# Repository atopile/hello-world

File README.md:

# hello-world

Wooohooo a new package!

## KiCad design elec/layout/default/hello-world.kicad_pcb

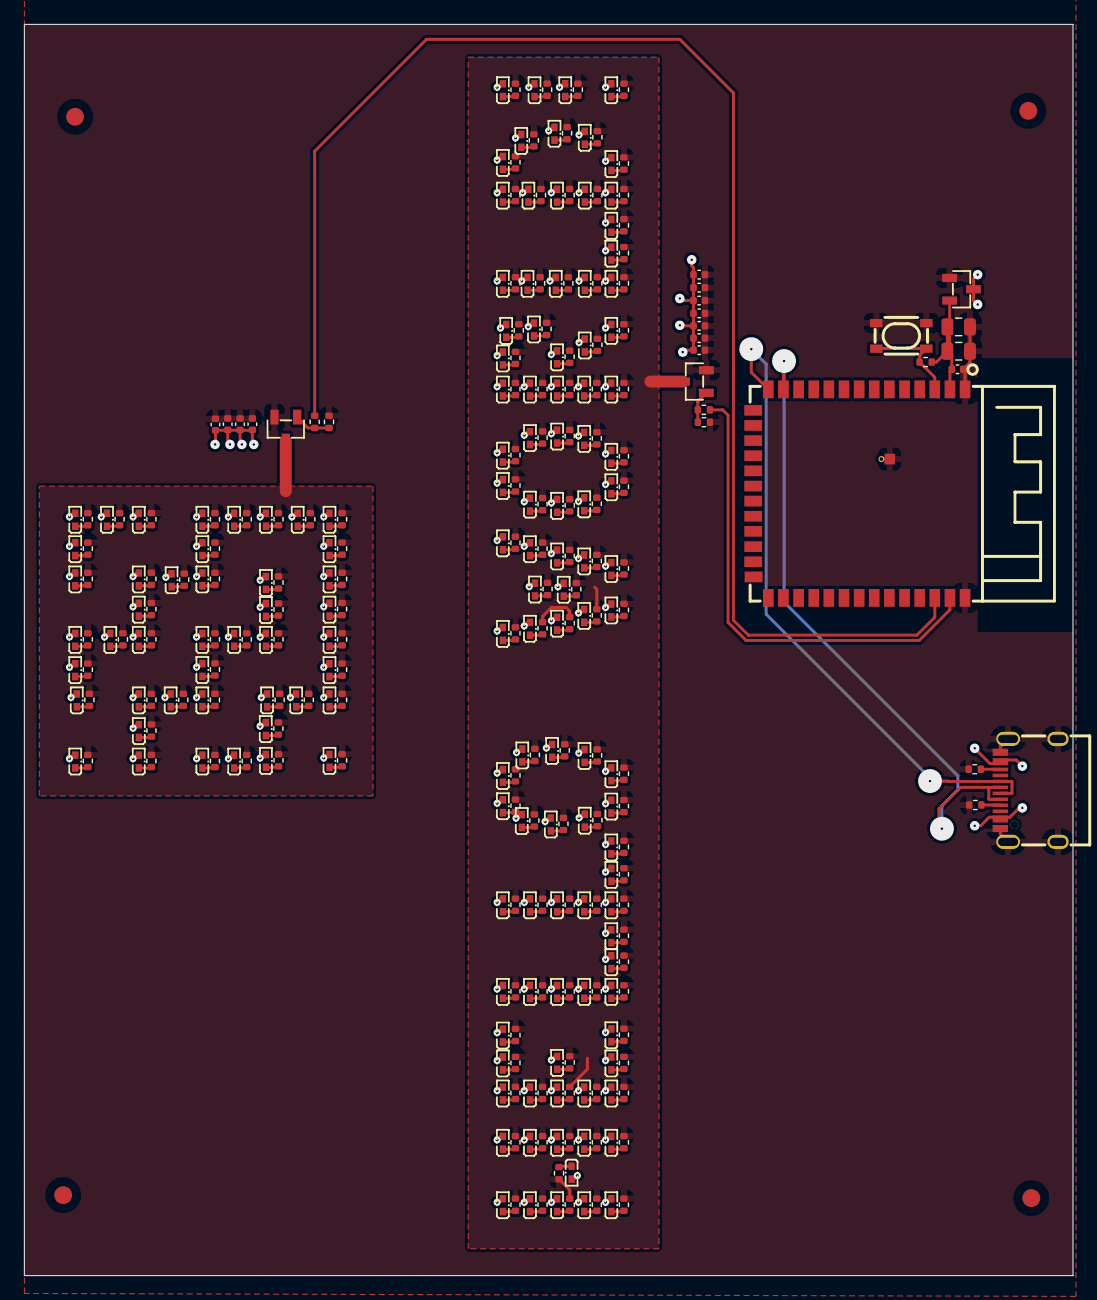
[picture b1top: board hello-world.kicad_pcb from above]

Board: 2 copper layers, 88.0 x 105.0 mm, 319 parts (0 on the bottom side), 158 nets.

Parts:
C1, C5, C6, C7, C8, C9, C10, C11, C12, C13, C14: 25V 1uF X5R ±10% 0402 Multilayer Ceramic Capacito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; C0402
C2: 16V 100nF X7R ±10% 0402 Multilayer Ceramic Capaci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; C0402
C3, C4: 25V 10uF X5R ±10% 0805 Multilayer Ceramic Capacit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; C0805
FID1, FID2, FID3, FID4: Fiducial_1.5mm_Mask3mm
LED1, LED2, LED3, LED4, LED5, LED6, LED7, LED8, LED9, LED10, LED11, LED12, LED13, LED14, LED15, LED16, LED17, LED18, LED19, LED20, LED21, LED22, LED23, LED24, LED25, LED26, LED27, LED28, LED29, LED30, LED31, LED32, LED33, LED34, LED35, LED36, LED37, LED38, LED39, LED40, LED41, LED42, LED43, LED44, LED45, LED46, LED47, LED48, LED49, LED50, LED51, LED52, LED53, LED54, LED55, LED56, LED57, LED58, LED59, LED60, LED61, LED62, LED63, LED64, LED65, LED66, LED67, LED68, LED69, LED70, LED71, LED72, LED73, LED74, LED75, LED76, LED77, LED78, LED79, LED80, LED81, LED82, LED83, LED84, LED85, LED86, LED87, LED88, LED89, LED90, LED91, LED92, LED93, LED94, LED95, LED96, LED97, LED98, LED99, LED100, LED101, LED102, LED103, LED104, LED105, LED106, LED107, LED108, LED109, LED110, LED111, LED112, LED113, LED114, LED115, LED116, LED117, LED118, LED119, LED120, LED121, LED122, LED123, LED124, LED125, LED126, LED127, LED128, LED129, LED130, LED131, LED132, LED133, LED134, LED135, LED136, LED137, LED138, LED139, LED140, LED141, LED142, LED143, LED144: ?; LED0402-RD_ORANGE
Q1, Q2: ?; SOT-23-3_L2.9-W1.3-P1.90-LS2.4-BR
R1, R2, R4, R5, R6, R7: 62.5mW Thick Film Resistors 50V ±100ppm/℃ ±1% 4.7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; R0402
R3: 62.5mW Thick Film Resistors 50V ±100ppm/℃ ±1% 10k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; R0402
R8, R9, R10, R11, R12, R13, R14, R15, R16, R17, R18, R19, R20, R21, R22, R23, R24, R25, R26, R27, R28, R29, R30, R31, R32, R33, R34, R35, R36, R37, R38, R39, R40, R41, R42, R43, R44, R45, R46, R47, R48, R49, R50, R51, R52, R53, R54, R55, R56, R57, R58, R59, R60, R61, R62, R63, R64, R65, R66, R67, R68, R69, R70, R71, R72, R73, R74, R75, R76, R77, R78, R79, R80, R81, R82, R83, R84, R85, R86, R87, R88, R89, R90, R91, R92, R93, R94, R95, R96, R97, R98, R99, R100, R101, R102, R103, R104, R105, R106, R107, R108, R109, R110, R111, R112, R113, R114, R115, R116, R117, R118, R119, R120, R121, R122, R123, R124, R125, R126, R127, R128, R129, R130, R131, R132, R133, R134, R135, R136, R137, R138, R139, R140, R141, R142, R143, R144, R145, R146, R147, R148, R149, R150, R151: 62.5mW Thick Film Resistors 50V ±100ppm/℃ ±1% 5.4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; R0402
U1: ?; USB-C-SMD_KH-TYPE-C-16P
U2: ?; SOT-23-3_L2.9-W1.3-P0.95-LS2.4-BR
U3: ?; WIRELM-SMD_ESP32-S3-WROOM-1
U4: ?; KEY-SMD_4P-L4.2-W3.2-P2.20-LS4.6

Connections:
3V3: C2.1, C3.1, C4.1, R3.1, U2.2, U3.2
5V: C1.1, C5.1, C6.1, C7.1, C8.1, C9.1, C10.1, C11.1, C12.1, C13.1, C14.1, LED1.2, LED2.2, LED3.2, LED4.2, LED5.2, LED6.2, LED7.2, LED8.2, LED9.2, LED10.2, LED11.2, LED12.2, LED13.2, LED14.2, LED15.2, LED16.2, LED17.2, LED18.2, LED19.2, LED20.2, LED21.2, LED22.2, LED23.2, LED24.2, LED25.2, LED26.2, LED27.2, LED28.2, LED29.2, LED30.2, LED31.2, LED32.2, LED33.2, LED34.2, LED35.2, LED36.2, LED37.2, LED38.2, LED39.2, LED40.2, LED41.2, LED42.2, LED43.2, LED44.2, LED45.2, LED46.2, LED47.2, LED48.2, LED49.2, LED50.2, LED51.2, LED52.2, LED53.2, LED54.2, LED55.2, LED56.2, LED57.2, LED58.2, LED59.2, LED60.2, LED61.2, LED62.2, LED63.2, LED64.2, LED65.2, LED66.2, LED67.2, LED68.2, LED69.2, LED70.2, LED71.2, LED72.2, LED73.2, LED74.2, LED75.2, LED76.2, LED77.2, LED78.2, LED79.2, LED80.2, LED81.2, LED82.2, LED83.2, LED84.2, LED85.2, LED86.2, LED87.2, LED88.2, LED89.2, LED90.2, LED91.2, LED92.2, LED93.2, LED94.2, LED95.2, LED96.2, LED97.2, LED98.2, LED99.2, LED100.2, LED101.2, LED102.2, LED103.2, LED104.2, LED105.2, LED106.2, LED107.2, LED108.2, LED109.2, LED110.2, LED111.2, LED112.2, LED113.2, LED114.2, LED115.2, LED116.2, LED117.2, LED118.2, LED119.2, LED120.2, LED121.2, LED122.2, LED123.2, LED124.2, LED125.2, LED126.2, LED127.2, LED128.2, LED129.2, LED130.2, LED131.2, LED132.2, LED133.2, LED134.2, LED135.2, LED136.2, LED137.2, LED138.2, LED139.2, LED140.2, LED141.2, LED142.2, LED143.2, LED144.2, U1.A4, U1.A9, U1.B4, U1.B9, U2.3
GND_HELLO_WORLD: Q1.3, R8.2, R9.2, R10.2, R11.2, R12.2, R13.2, R14.2, R15.2, R16.2, R17.2, R18.2, R19.2, R20.2, R21.2, R22.2, R23.2, R24.2, R25.2, R26.2, R27.2, R28.2, R29.2, R30.2, R31.2, R32.2, R33.2, R34.2, R35.2, R36.2, R37.2, R38.2, R39.2, R40.2, R41.2, R42.2, R43.2, R44.2, R45.2, R46.2, R47.2, R48.2, R49.2, R50.2, R51.2, R52.2, R53.2, R54.2, R55.2, R56.2, R57.2, R58.2, R59.2, R60.2, R61.2, R62.2, R63.2, R64.2, R65.2, R66.2, R67.2, R68.2, R69.2, R70.2, R71.2, R72.2, R73.2, R74.2, R75.2, R76.2, R77.2, R78.2, R79.2, R80.2, R81.2, R82.2, R83.2, R84.2, R85.2, R86.2, R87.2, R88.2, R89.2, R90.2, R91.2, R92.2, R93.2, R94.2, R95.2, R96.2, R97.2, R98.2, R99.2, R100.2, R101.2, R102.2, R103.2, R104.2, R105.2, R106.2
GND_LOGO: Q2.3, R107.2, R108.2, R109.2, R110.2, R111.2, R112.2, R113.2, R114.2, R115.2, R116.2, R117.2, R118.2, R119.2, R120.2, R121.2, R122.2, R123.2, R124.2, R125.2, R126.2, R127.2, R128.2, R129.2, R130.2, R131.2, R132.2, R133.2, R134.2, R135.2, R136.2, R137.2, R138.2, R139.2, R140.2, R141.2, R142.2, R143.2, R144.2, R145.2, R146.2, R147.2, R148.2, R149.2, R150.2, R151.2
cc1: R1.1, U1.A5
cc2: R2.1, U1.B5
dm: U1.A7, U1.B7, U3.13
dp: U1.A6, U1.B6, U3.14
en: R3.2, U3.3, U4.1, U4.2
esp32.ic-vcc: R4.1, U3.39
esp32.ic-vcc-1: R6.1, U3.38
gnd: C1.2, C2.2, C3.2, C4.2, C5.2, C6.2, C7.2, C8.2, C9.2, C10.2, C11.2, C12.2, C13.2, C14.2, Q1.2, Q2.2, R1.2, R2.2, R5.1, R7.1, U1.1, U1.2, U1.3, U1.4, U1.A1, U1.A12, U1.B1, U1.B12, U2.1, U3.1, U3.40, U3.41, U4.3, U4.4
hello_world_switch.fet-gate: Q1.1, R4.2, R5.2
led1.indicator.resistor-cathode: LED1.1, R8.1
led2.indicator.resistor-cathode: LED2.1, R9.1
led3.indicator.resistor-cathode: LED3.1, R10.1
led4.indicator.resistor-cathode: LED4.1, R11.1
led5.indicator.resistor-cathode: LED5.1, R12.1
led6.indicator.resistor-cathode: LED6.1, R13.1
led7.indicator.resistor-cathode: LED7.1, R14.1
led8.indicator.resistor-cathode: LED8.1, R15.1
led9.indicator.resistor-cathode: LED9.1, R16.1
led10.indicator.resistor-cathode: LED10.1, R17.1
led11.indicator.resistor-cathode: LED11.1, R18.1
led12.indicator.resistor-cathode: LED12.1, R19.1
led13.indicator.resistor-cathode: LED13.1, R20.1
led14.indicator.resistor-cathode: LED14.1, R21.1
led15.indicator.resistor-cathode: LED15.1, R22.1
led16.indicator.resistor-cathode: LED16.1, R23.1
led17.indicator.resistor-cathode: LED17.1, R24.1
led18.indicator.resistor-cathode: LED18.1, R25.1
led19.indicator.resistor-cathode: LED19.1, R26.1
led20.indicator.resistor-cathode: LED20.1, R27.1
led21.indicator.resistor-cathode: LED21.1, R28.1
led22.indicator.resistor-cathode: LED22.1, R29.1
led23.indicator.resistor-cathode: LED23.1, R30.1
led24.indicator.resistor-cathode: LED24.1, R31.1
led25.indicator.resistor-cathode: LED25.1, R32.1
led26.indicator.resistor-cathode: LED26.1, R33.1
led27.indicator.resistor-cathode: LED27.1, R34.1
led28.indicator.resistor-cathode: LED28.1, R35.1
led29.indicator.resistor-cathode: LED29.1, R36.1
led30.indicator.resistor-cathode: LED30.1, R37.1
led31.indicator.resistor-cathode: LED31.1, R38.1
led33.indicator.resistor-cathode: LED32.1, R39.1
led34.indicator.resistor-cathode: LED33.1, R40.1
led35.indicator.resistor-cathode: LED34.1, R41.1
led36.indicator.resistor-cathode: LED35.1, R42.1
led37.indicator.resistor-cathode: LED36.1, R43.1
led38.indicator.resistor-cathode: LED37.1, R44.1
led39.indicator.resistor-cathode: LED38.1, R45.1
led40.indicator.resistor-cathode: LED39.1, R46.1
led41.indicator.resistor-cathode: LED40.1, R47.1
led42.indicator.resistor-cathode: LED41.1, R48.1
led43.indicator.resistor-cathode: LED42.1, R49.1
led44.indicator.resistor-cathode: LED43.1, R50.1
led45.indicator.resistor-cathode: LED44.1, R51.1
led46.indicator.resistor-cathode: LED45.1, R52.1
led47.indicator.resistor-cathode: LED46.1, R53.1
led48.indicator.resistor-cathode: LED47.1, R54.1
led49.indicator.resistor-cathode: LED48.1, R55.1
led50.indicator.resistor-cathode: LED49.1, R56.1
led51.indicator.resistor-cathode: LED50.1, R57.1
led52.indicator.resistor-cathode: LED51.1, R58.1
led53.indicator.resistor-cathode: LED52.1, R59.1
led54.indicator.resistor-cathode: LED53.1, R60.1
led55.indicator.resistor-cathode: LED54.1, R61.1
led56.indicator.resistor-cathode: LED55.1, R62.1
led57.indicator.resistor-cathode: LED56.1, R63.1
led58.indicator.resistor-cathode: LED57.1, R64.1
led59.indicator.resistor-cathode: LED58.1, R65.1
led60.indicator.resistor-cathode: LED59.1, R66.1
led61.indicator.resistor-cathode: LED60.1, R67.1
led62.indicator.resistor-cathode: LED61.1, R68.1
led63.indicator.resistor-cathode: LED62.1, R69.1
led64.indicator.resistor-cathode: LED63.1, R70.1
led65.indicator.resistor-cathode: LED64.1, R71.1
led66.indicator.resistor-cathode: LED65.1, R72.1
led67.indicator.resistor-cathode: LED66.1, R73.1
led68.indicator.resistor-cathode: LED67.1, R74.1
led69.indicator.resistor-cathode: LED68.1, R75.1
led70.indicator.resistor-cathode: LED69.1, R76.1
led71.indicator.resistor-cathode: LED70.1, R77.1
led72.indicator.resistor-cathode: LED71.1, R78.1
led73.indicator.resistor-cathode: LED72.1, R79.1
led74.indicator.resistor-cathode: LED73.1, R80.1
led75.indicator.resistor-cathode: LED74.1, R81.1
led76.indicator.resistor-cathode: LED75.1, R82.1
led77.indicator.resistor-cathode: LED76.1, R83.1
led78.indicator.resistor-cathode: LED77.1, R84.1
led79.indicator.resistor-cathode: LED78.1, R85.1
led80.indicator.resistor-cathode: LED79.1, R86.1
led81.indicator.resistor-cathode: LED80.1, R87.1
led82.indicator.resistor-cathode: LED81.1, R88.1
led83.indicator.resistor-cathode: LED82.1, R89.1
led84.indicator.resistor-cathode: LED83.1, R90.1
led85.indicator.resistor-cathode: LED84.1, R91.1
led86.indicator.resistor-cathode: LED85.1, R92.1
led87.indicator.resistor-cathode: LED86.1, R93.1
led88.indicator.resistor-cathode: LED87.1, R94.1
led89.indicator.resistor-cathode: LED88.1, R95.1
led90.indicator.resistor-cathode: LED89.1, R96.1
led91.indicator.resistor-cathode: LED90.1, R97.1
led92.indicator.resistor-cathode: LED91.1, R98.1
led93.indicator.resistor-cathode: LED92.1, R99.1
led94.indicator.resistor-cathode: LED93.1, R100.1
led95.indicator.resistor-cathode: LED94.1, R101.1
led96.indicator.resistor-cathode: LED95.1, R102.1
led97.indicator.resistor-cathode: LED96.1, R103.1
led98.indicator.resistor-cathode: LED97.1, R104.1
led99.indicator.resistor-cathode: LED98.1, R105.1
led100.indicator.resistor-cathode: LED99.1, R106.1
led_logo1.indicator.resistor-cathode: LED100.1, R107.1
led_logo2.indicator.resistor-cathode: LED101.1, R108.1
led_logo3.indicator.resistor-cathode: LED102.1, R109.1
led_logo4.indicator.resistor-cathode: LED103.1, R110.1
led_logo5.indicator.resistor-cathode: LED104.1, R111.1
led_logo6.indicator.resistor-cathode: LED105.1, R112.1
led_logo7.indicator.resistor-cathode: LED106.1, R113.1
led_logo8.indicator.resistor-cathode: LED107.1, R114.1
led_logo10.indicator.resistor-cathode: LED108.1, R115.1
led_logo11.indicator.resistor-cathode: LED109.1, R116.1
led_logo12.indicator.resistor-cathode: LED110.1, R117.1
led_logo13.indicator.resistor-cathode: LED111.1, R118.1
led_logo14.indicator.resistor-cathode: LED112.1, R119.1
led_logo15.indicator.resistor-cathode: LED113.1, R120.1
led_logo16.indicator.resistor-cathode: LED114.1, R121.1
led_logo17.indicator.resistor-cathode: LED115.1, R122.1
led_logo18.indicator.resistor-cathode: LED116.1, R123.1
led_logo19.indicator.resistor-cathode: LED117.1, R124.1
led_logo20.indicator.resistor-cathode: LED118.1, R125.1
led_logo21.indicator.resistor-cathode: LED119.1, R126.1
led_logo22.indicator.resistor-cathode: LED120.1, R127.1
led_logo23.indicator.resistor-cathode: LED121.1, R128.1
led_logo25.indicator.resistor-cathode: LED122.1, R129.1
led_logo26.indicator.resistor-cathode: LED123.1, R130.1
led_logo27.indicator.resistor-cathode: LED124.1, R131.1
led_logo28.indicator.resistor-cathode: LED125.1, R132.1
led_logo29.indicator.resistor-cathode: LED126.1, R133.1
led_logo30.indicator.resistor-cathode: LED127.1, R134.1
led_logo31.indicator.resistor-cathode: LED128.1, R135.1
led_logo32.indicator.resistor-cathode: LED129.1, R136.1
led_logo33.indicator.resistor-cathode: LED130.1, R137.1
led_logo34.indicator.resistor-cathode: LED131.1, R138.1
led_logo35.indicator.resistor-cathode: LED132.1, R139.1
led_logo36.indicator.resistor-cathode: LED133.1, R140.1
led_logo37.indicator.resistor-cathode: LED134.1, R141.1
led_logo38.indicator.resistor-cathode: LED135.1, R142.1
led_logo40.indicator.resistor-cathode: LED136.1, R143.1
led_logo41.indicator.resistor-cathode: LED137.1, R144.1
led_logo42.indicator.resistor-cathode: LED138.1, R145.1
led_logo43.indicator.resistor-cathode: LED139.1, R146.1
led_logo45.indicator.resistor-cathode: LED140.1, R147.1
led_logo46.indicator.resistor-cathode: LED141.1, R148.1
led_logo47.indicator.resistor-cathode: LED142.1, R149.1
led_logo48.indicator.resistor-cathode: LED143.1, R150.1
led_logo49.indicator.resistor-cathode: LED144.1, R151.1
logo_switch.fet-gate: Q2.1, R6.2, R7.2

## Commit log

2024-10-18 Configure project
2024-10-31 initial build
2024-11-08 rotat 90 degrees and move to kicad X0Y0
